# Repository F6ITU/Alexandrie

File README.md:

# Alexandrie

  **Pour plus d'informations, consultez le Wiki associé à cette page**
  **For more information, see the Wiki associated with this page**
  
Kicad files

Control board for Alexiares filter set

This work is protected by the TAPR Open Hardware Licence https://www.tapr.org/ohl.html

Original work by Graham Haddock, KE9H and Phil Harman, VK6APH.

This board supports the SPI "Alexiares" protocol (also called "J16") of 
the original Hermes SDR board designed by the OpenHPSDR group.

As Alexiares was not sold anymore by the TAPR, a new and more "modular" 
design was needed by many hams wishing to play with OpenHPSDR plateforms
(Homebrewed Hermes or Angelia boards, Steve KF7O's Hermes Lite, Red Pitaya 
supporting Pavel Denim's firmware... ) 

Alexandrie is only needed by people using an original 
Hermes Board or a Red Pitaya (via the SPI output)

A specific replacement board (Alexi2C) has been design for 

* Hermes, Angelia, Odyssey2, HiQSDR boards
*  Red Pitaya owners using the I2C output

3D image of the board are stored on this repo

Alexandrie dwn.jpg

Alexandrie up.jpg

Board's dimensions are oversized to fit the 5x10 and 10x10cm 
size of all board of the Hermes project under Kicad: 

AlexI2C

Alexandrie (this one)

Alexiares_Coax_Out

Alexiares_HPF

Alexiares_LPF

Mentor

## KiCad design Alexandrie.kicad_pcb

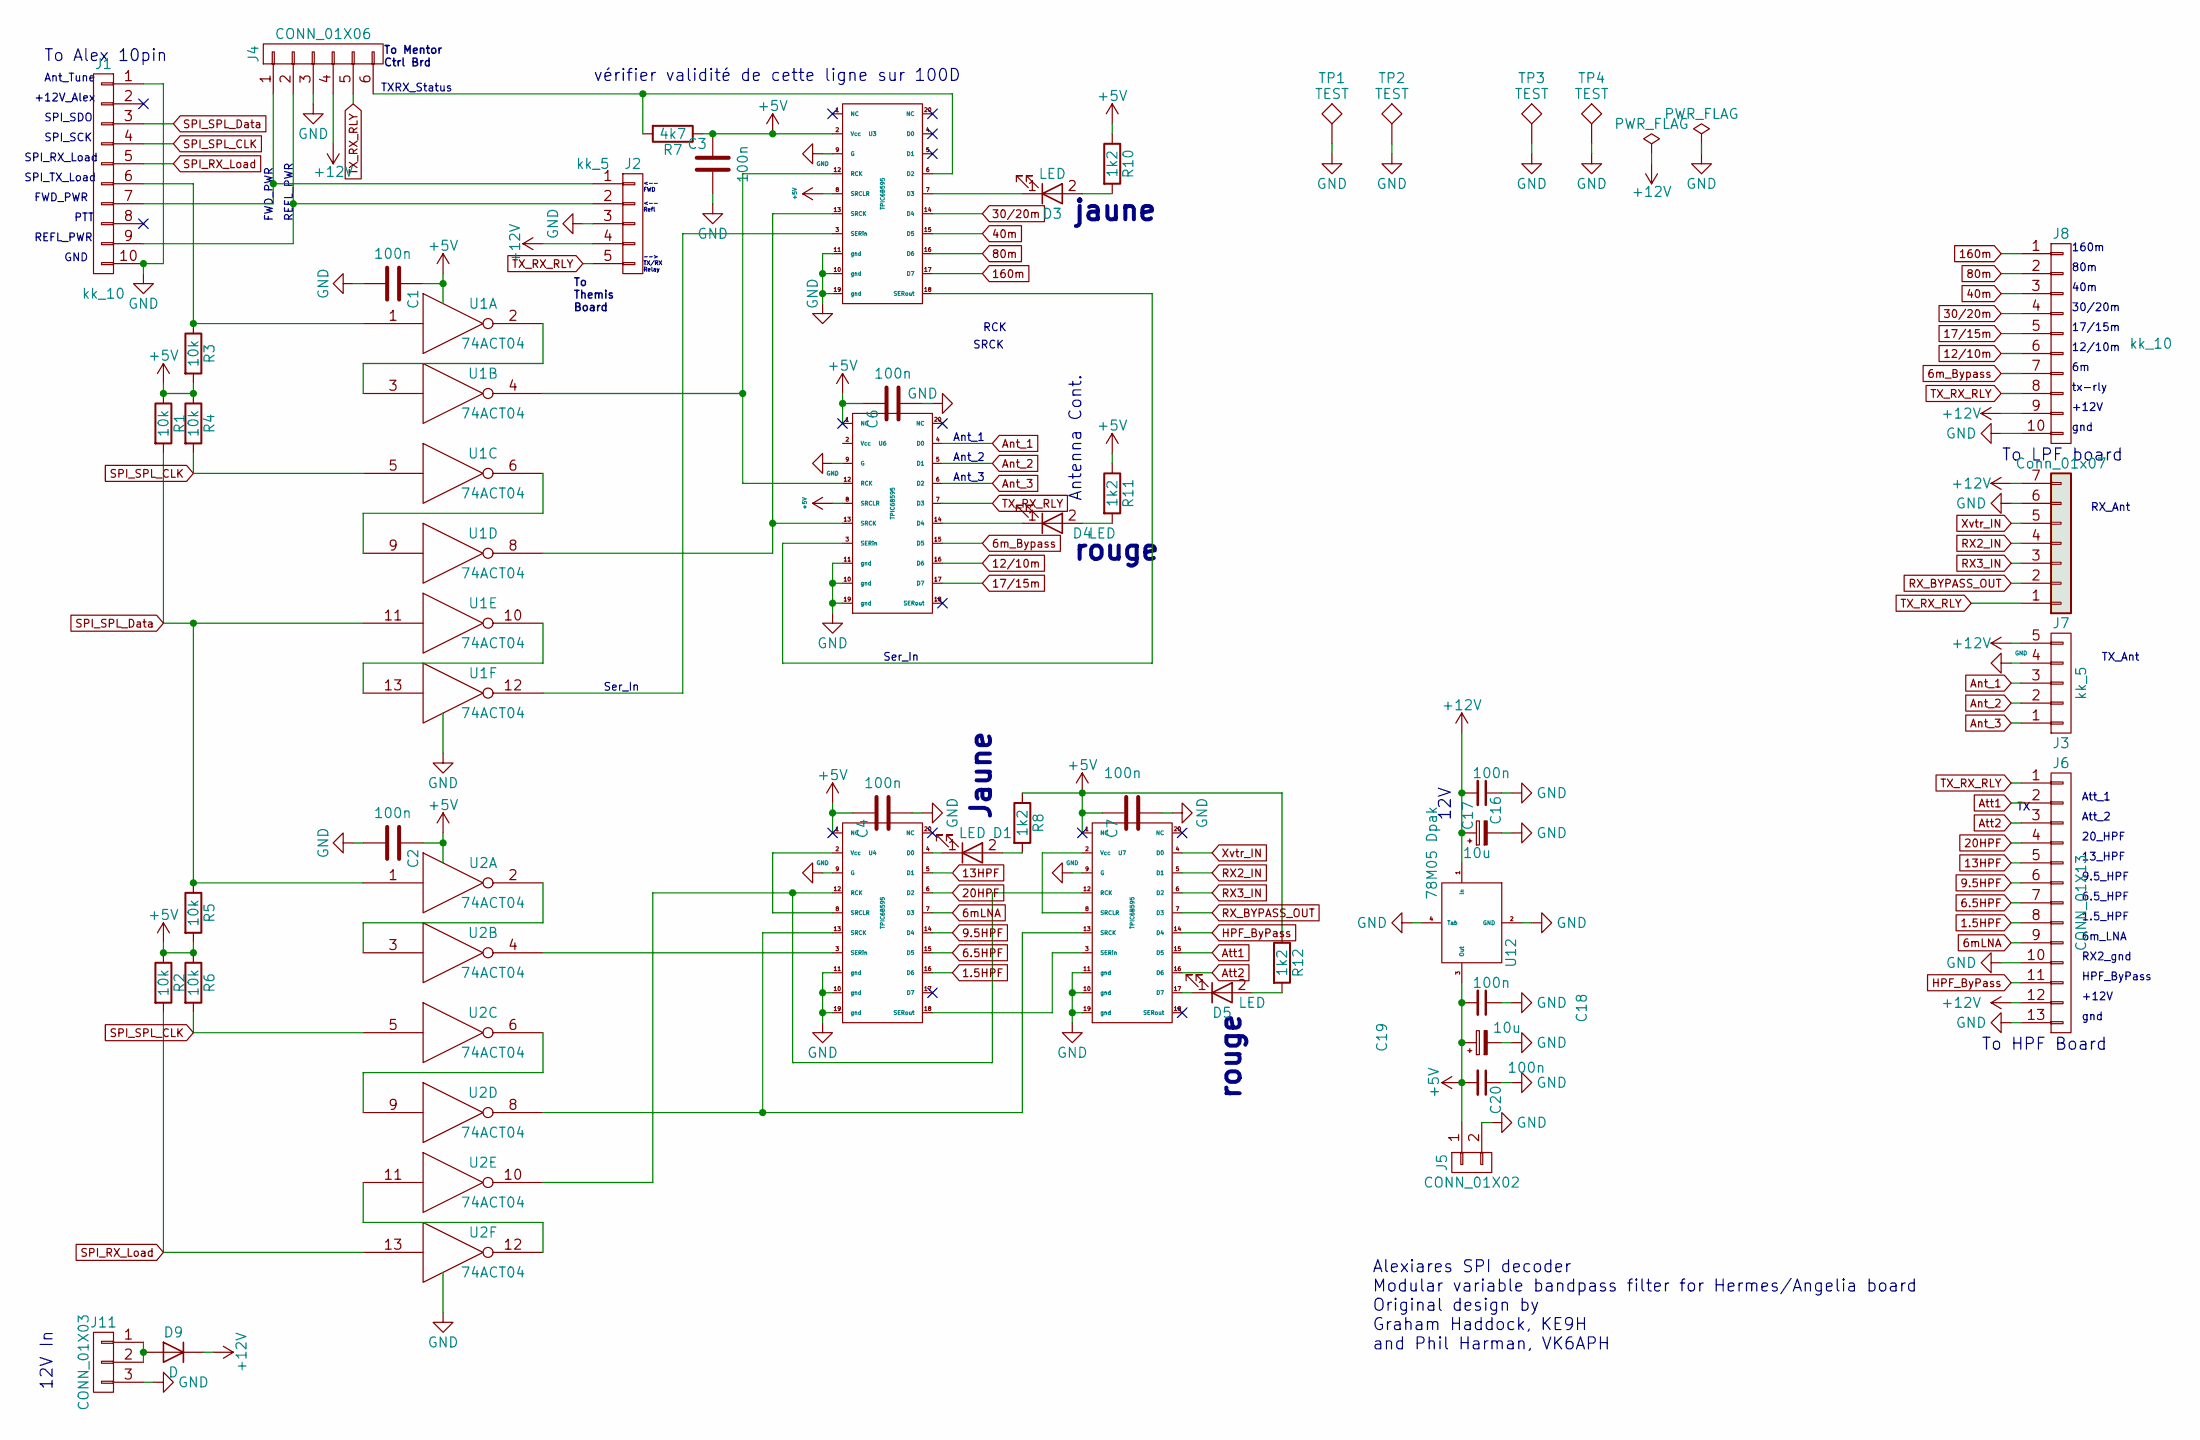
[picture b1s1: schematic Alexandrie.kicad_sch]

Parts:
C1, C2, C3, C4, C6, C7, C16, C18, C20: 100n; C_0805_2012Metric_Pad1.18x1.45mm_HandSolder
C17, C19: 10u; CP_Tantalum_Case-C_EIA-6032-28_Hand
D1, D3, D4, D5: LED; LED_1206_3216Metric_Pad1.42x1.75mm_HandSolder
D9: D; D_SMB_Handsoldering
J1, J8: kk_10; kk100_22-23-2101
J2, J3: kk_5; kk100_22-23-2051
J4: CONN_01X06; kk100_22-23-2061
J5: CONN_01X02; kk100_22-23-2021
J6: CONN_01X13; kk100_22-23-2131
J7: Conn_01x07; Molex_KK-6410-07_07x2.54mm_Straight
J11: CONN_01X03; kk100_22-23-2031
R1, R2, R3, R4, R5, R6: 10k; R_0805_2012Metric_Pad1.20x1.40mm_HandSolder
R7: 4k7; R_0805_2012Metric_Pad1.20x1.40mm_HandSolder
R8, R10, R11, R12: 1k2; R_0805_2012Metric_Pad1.20x1.40mm_HandSolder
TP1, TP2, TP3, TP4: TEST; MountingHole_3.5mm_Pad
U1, U2: 74ACT04; SO-14_3.9x8.65mm_P1.27mm
U3, U4, U6, U7: TPIC6B595; SO-20_12.8x7.5mm_P1.27mm
U12: 78M05 Dpak; TO-263-3_TabPin4

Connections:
1.5HPF: J6.8, U4.16 (D6)
6.5HPF: J6.7, U4.15 (D5)
6mLNA: J6.9, U4.7 (D3)
6m_Bypass: J8.7, U6.15 (D5)
9.5HPF: J6.6, U4.14 (D4)
12/10m: J8.6, U6.16 (D6)
13HPF: J6.5, U4.5 (D1)
17/15m: J8.5, U6.17 (D7)
20HPF: J6.4, U4.6 (D2)
30/20m: J8.4, U3.14 (D4)
40m: J8.3, U3.15 (D5)
80m: J8.2, U3.16 (D6)
160m: J8.1, U3.17 (D7)
+5V: C1.1, C2.1, C3.1, C4.1, C6.1, C7.1, C18.2, C19.1, C20.2, J5.1, R1.1, R2.1, R3.2, R4.1, R5.2, R6.1, R7.1, R8.1, R10.1, R11.1, R12.1, U1.14 (VCC), U2.14 (VCC), U3.2 (Vcc), U3.8 (SRCLR), U4.1 (NC), U6.1 (NC), U6.8 (SRCLR), U7.1 (NC), U12.3 (Out)
+12V: C16.2, C17.1, D9.1 (K), J2.4, J3.5, J4.4, J6.12, J7.7, J8.9, U12.1 (In)
Ant_1: J3.3, U6.4 (D0)
Ant_2: J3.2, U6.5 (D1)
Ant_3: J3.1, U6.6 (D2)
Att1: J6.2, U7.15 (D5)
Att2: J6.3, U7.16 (D6)
GND: C1.2, C2.2, C3.2, C4.2, C6.2, C7.2, C16.1, C17.2, C18.1, C19.2, C20.1, J1.1, J1.10, J2.3, J3.4, J4.3, J5.2, J6.10, J6.13, J7.6, J8.10, J11.3, TP1.1, TP2.1, TP3.1, TP4.1, U1.7 (GND), U2.7 (GND), U3.9 (G), U3.10 (gnd), U3.11 (gnd), U3.19 (gnd), U4.9 (G), U4.10 (gnd), U4.11 (gnd), U4.19 (gnd), U6.9 (G), U6.10 (gnd), U6.11 (gnd), U6.19 (gnd), U7.9 (G), U7.10 (gnd), U7.11 (gnd), U7.19 (gnd), U12.2 (GND), U12.4 (Tab)
HPF_ByPass: J6.11, U7.14 (D4)
unnamed: D1.1 (K), U4.4 (D0)
unnamed: D1.2 (A), R8.2
unnamed: D3.1 (K), U3.7 (D3)
unnamed: D3.2 (A), R10.2
unnamed: D4.1 (K), U6.14 (D4)
unnamed: D4.2 (A), R11.2
unnamed: D5.1 (K), U7.17 (D7)
unnamed: D5.2 (A), R12.2
unnamed: D9.2 (A), J11.1, J11.2
unnamed: J1.6, R3.1, U1.1
unnamed: J1.7, J2.1, J4.1
unnamed: J1.9, J2.2, J4.2
unnamed: J4.6, R7.2, U3.6 (D2)
unnamed: U1.2, U1.3
unnamed: U1.4, U3.12 (RCK), U6.12 (RCK)
unnamed: U1.6, U1.9
unnamed: U1.8, U3.13 (SRCK), U6.13 (SRCK)
unnamed: U1.10, U1.13
unnamed: U1.12, U3.3 (SERin)
unnamed: U2.2, U2.3
unnamed: U2.4, U4.3 (SERin)
unnamed: U2.6, U2.9
unnamed: U2.8, U4.13 (SRCK), U7.13 (SRCK)
unnamed: U2.10, U4.12 (RCK), U7.12 (RCK)
unnamed: U2.11, U2.12
unnamed: U3.18 (SERout), U6.3 (SERin)
unnamed: U4.2 (Vcc), U4.8 (SRCLR)
unnamed: U4.18 (SERout), U7.3 (SERin)
unnamed: U7.2 (Vcc), U7.8 (SRCLR)
RX2_IN: J7.4, U7.5 (D1)
RX3_IN: J7.3, U7.6 (D2)
RX_BYPASS_OUT: J7.2, U7.7 (D3)
SPI_RX_Load: J1.5, R2.2, U2.13
SPI_SPL_CLK: J1.4, R4.2, R6.2, U1.5, U2.5
SPI_SPL_Data: J1.3, R1.2, R5.1, U1.11, U2.1
TX_RX_RLY: J2.5, J4.5, J6.1, J7.1, J8.8, U6.7 (D3)
Xvtr_IN: J7.5, U7.4 (D0)

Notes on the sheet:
20_HPF
SRCK
SPI_SDO
To HPF Board
160m
FWD_PWR
Jaune
17/15m
PTT
6.5_HPF
Ant_1
Antenna Cont.
1.5_HPF
SPI_SCK
<-- Refl
tx-rly
Ant_3
REFL_PWR
jaune
9.5_HPF
80m
TXRX_Status
To Themis Board
<-- FWD
6m_LNA
Att_1
To Alex 10pin
gnd
12/10m
RCK
--> TX/RX Relay
30/20m
Ser_In
RX_Ant
GND
Alexiares SPI decoder Modular variable bandpass filter for Hermes/Angelia board Original design by Graham Haddock, KE9H and Phil Harman, VK6APH
rouge
Ant_Tune
RX2_gnd
40m

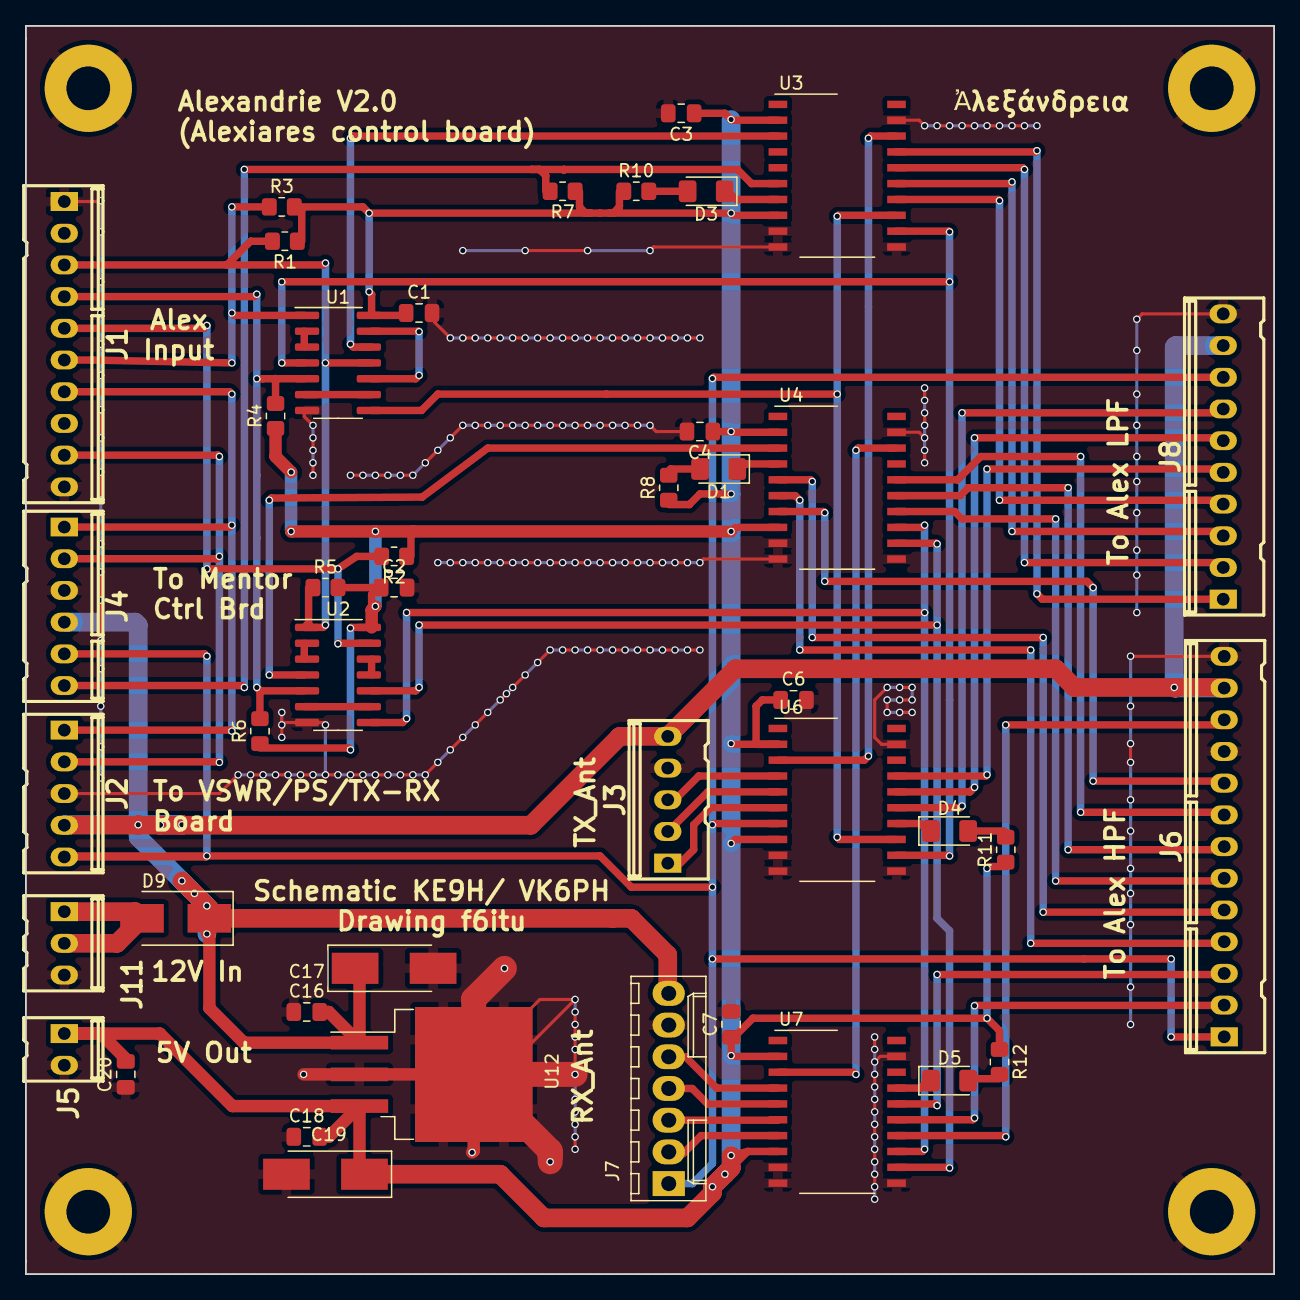
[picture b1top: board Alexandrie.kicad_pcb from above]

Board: 2 copper layers, 100.0 x 100.0 mm, 47 parts (0 on the bottom side), 59 nets.

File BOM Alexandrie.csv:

Component Count:,43,,,,
Ref,Value,Footprint,Datasheet,Manufacturer,Vendor
C1,100n,Capacitors_SMD:C_0805_HandSoldering,,,
C2,100n,Capacitors_SMD:C_0805_HandSoldering,,,
C3,100n,Capacitors_SMD:C_0805_HandSoldering,,,
C4,100n,Capacitors_SMD:C_0805_HandSoldering,,,
C6,100n,Capacitors_SMD:C_0805_HandSoldering,,,
C7,100n,Capacitors_SMD:C_0805_HandSoldering,,,
C16,100n,Capacitors_SMD:C_0805_HandSoldering,,,
C17,10u,Capacitors_Tantalum_SMD:CP_Tantalum_Case-C_EIA-6032-28_Hand,,,
C18,100n,Capacitors_SMD:C_0805_HandSoldering,,,
C19,10u,Capacitors_Tantalum_SMD:CP_Tantalum_Case-C_EIA-6032-28_Hand,,,
C20,100n,Capacitors_SMD:C_0805_HandSoldering,,,
D1,LED,smd_leds:Led_1206,,,
D3,LED,smd_leds:Led_1206,,,
D4,LED,smd_leds:Led_1206,,,
D5,LED,smd_leds:Led_1206,,,
D9,D,Diodes_SMD:D_SMB_Handsoldering,,,
J1,kk_10,conn_kk100:kk100_22-23-2101,,,
J2,kk_5,conn_kk100:kk100_22-23-2051,,,
J3,kk_5,conn_kk100:kk100_22-23-2051,,,
J4,CONN_01X06,conn_kk100:kk100_22-23-2061,,,
J5,CONN_01X02,conn_kk100:kk100_22-23-2021,,,
J6,CONN_01X13,conn_kk100:kk100_22-23-2131,,,
J7,CONN_01X06,conn_kk100:kk100_22-23-2061,,,
J8,kk_10,conn_kk100:kk100_22-23-2101,,,
J11,CONN_01X03,conn_kk100:kk100_22-23-2031,,,
R1,10k,Resistors_SMD:R_0805_HandSoldering,,,
R2,10k,Resistors_SMD:R_0805_HandSoldering,,,
R3,10k,Resistors_SMD:R_0805_HandSoldering,,,
R4,10k,Resistors_SMD:R_0805_HandSoldering,,,
R5,10k,Resistors_SMD:R_0805_HandSoldering,,,
R6,10k,Resistors_SMD:R_0805_HandSoldering,,,
R7,4k7,Resistors_SMD:R_0805_HandSoldering,,,
R8,1k2,Resistors_SMD:R_0805_HandSoldering,,,
R10,1k2,Resistors_SMD:R_0805_HandSoldering,,,
R11,1k2,Resistors_SMD:R_0805_HandSoldering,,,
R12,1k2,Resistors_SMD:R_0805_HandSoldering,,,
U1,74HCT04,Housings_SOIC:SOIC-14_3.9x8.7mm_Pitch1.27mm,,,
U2,74HCT04,Housings_SOIC:SOIC-14_3.9x8.7mm_Pitch1.27mm,,,
U3,TPIC6B595,Housings_SOIC:SO-20_12.8x7.5mm_Pitch1.27mm,,,
U4,TPIC6B595,Housings_SOIC:SO-20_12.8x7.5mm_Pitch1.27mm,,,
U6,TPIC6B595,Housings_SOIC:SO-20_12.8x7.5mm_Pitch1.27mm,,,
U7,TPIC6B595,Housings_SOIC:SO-20_12.8x7.5mm_Pitch1.27mm,,,
U12,78M05,Dpak,,,

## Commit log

2017-05-22 creation du depot Alexandrie
2017-05-23 schematic without power regulators
2017-05-23 ajout schema format pdf
2017-05-23 Angelia lpf/hpf Control board
2017-05-23 New English readme file
2017-05-25 final schematic drawing
2017-05-27 minor schematic errors fixed
2017-05-28 Alexandrie V 1.0 pcb routing w/o power supply
2017-05-29 final beta, Sylkmask to annotate
2017-05-29 RTM, sylkmask to do
2017-05-31 RTM with sylkmask
2017-06-12 Complete redrawing, Alexiares compatible
2017-10-03 some minor cleaning
2017-11-01 RTM 1
2017-11-02 Silk Screen errors fixed
2017-11-02 Readme cleaning, add 2 3D pictures
2017-11-02 Readme cleanup
2017-11-27 new footprint for drivers
2017-12-30 minor changes, BOM added
2017-12-30 Gerber files added
2018-01-05 via stitching added, new gerber
2018-01-13 silk cleaning
2018-01-21 new gerber, minor mods
2018-02-12 rx_bypass_out added on alexandrie
2018-02-12 hasl border added
2018-03-13 minor changes, silkmask mostly
2018-07-20 stable V2.0
2019-03-15 upgrate to Kicad 5.0n, new up to date Gerber
2020-07-23 cleaning, new bom and interactive bom
2020-09-05 Gerber added
2023-04-13 last commit, project deprecated, replaced by AlexV2
2026-05-17 kicad 10 update, new readme, new Wiki
